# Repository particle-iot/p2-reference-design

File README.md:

# P2 evaluation board reference design

This board is a reference design for creating your own P2 base board. 

It is not available for purchase as a completed product; if you are interested in prototyping with the P2 we recommend using the Photon 2, which contains a P2 module on it, and has the same pinouts as the Feather connectors on this board.

This is a simple breakout board for Particle's P2 Wi-Fi module. It breaks out all of its pins via easy to use headers. The board features a USB port, a barrel jack power connector, buttons, and RGB LED as well as Feather, Grove, and Qwiic connectors for prototyping with external sensors, displays, etc..

- [P2 Datasheet](https://docs.particle.io/reference/datasheets/wi-fi/p2-datasheet/)
- [Particle hardware library for Eagle CAD](https://github.com/particle-iot/hardware-libraries)

## Schematic

The schematic files (*.sch) in Eagle CAD format are included in the **eagle** directory in this repository.

## Board layout

The board layout files (*.brd) in Eagle CAD format are included in the **eagle** directory in this repository. 

This is a 4-layer board, so you won't be able to edit the board using the free version of Autodesk Eagle, however gerber files are included in the **gerbers** directory if you want to fabricate this exact board.

The recommended stack-up is:

- DIELECTRIC = 3.61 at 1GHz
- TOP LAYER = 1.7MIL (1 OZ)
- PREPEG = 7.96MIL
- LAYER 2 = 0.68MIL (0.5 OZ)
- CORE = 47MIL
- LAYER 3 = 0.68MIL (0.5 OZ)
- PREPEG = 7.96MIL
- BOTTOM LAYER = 1.7MIL (1 OZ)

## Description

| Label | Description |
| :---: | :--- |
|     1 | USB |
|     2 | 5V Power In (optional) |
|     3 | P2 Module |
|     4 | External Wi-Fi and BLE antenna (optional) |
|     5 | Feather expansion connector |
|     6 | Qwiic I2C connector |
|     7 | Feather expansion connector |
|     8 | Grove expansion connector |
|     9 | Expansion header|
|    10 | RESET button |
|    11 | RGB LED |
|    12 | MODE button|
|    13 | SWD debugging connector |

If powering by USB, 500 mA is required. This a compatible with most USB hubs, computers, laptops, and chargers, but will not work with some low-power USB ports on some keyboards.
 
The P2 includes a built-in trace antenna that is used for both BLE and Wi-Fi. A U.FL connector is provided for an external antenna, if desired. The antenna selection must be made in software; the P2 will not automatically switch between built-in and external antennas. If using an external antenna, a dual-band (2.4 GHz and 5 GHz) antenna is required. The external antenna doesn't have to explicitly include BLE support, as the BLE frequencies are the same as 2.4 GHz Wi-Fi so all dual-band Wi-Fi antennas are compatible.

## Building user firmware

As of the time of writing (June 2022), P2 firmware can only be compiled using the cloud compiler.

### Using Particle Workbench

When using Particle Workbench, use the **Particle: Launch CLI** option from the Command Palette (Command-Shift-P or Ctrl-Shift-P). Then use the Particle CLI to generate a binary, as described in the next section.

### Using the Particle CLI

From the Particle CLI, you can use a command such as:

```
particle compile p2 . --target 5.3.1 --saveTo firmware.bin
```

Note that you must specify a target system version when building for the P2. If an upgrade of Device OS is required, it will be updated OTA.

### Using the Web IDE

From the Web IDE, select the Devices icon, then your P2 device, then target an appropriate firmware version, such as 5.3.1. If an upgrade of Device OS is required, it will be updated OTA.

## Expansion connectors

### Expansion header

If you are prototyping your own custom design you may want to use the 40-pin expansion header. It's a standard 20x2 female header, 0.1" pitch, that can accept male header pins or prototyping wires.

See the [P2 Datasheet](https://docs.particle.io/reference/datasheets/wi-fi/p2-datasheet/) for details about the pins. The gold boxes indicate the P2 pin numbers.

### Feather expansion

There are two socket for [Feather accessory boards](https://docs.particle.io/hardware/expansion/feather/). These are only for use with displays, sensors, storage, etc.. 

You must not plug a Particle device such as an Argon or Boron in this socket, as the device may be permanently damaged.

This will work with most Feather boards, however:

- The P2 does not support ADC inputs A3, A4, and A5.
- The P2 does not work with Feather accessories that use SPI1 on the Argon or Boron D pins.
- Some pins have different names which may require minor source code modifications. This includes and code that used Argon or Boron pins A3, A4, A5, or D8.

The pinouts of the Feather accessory socket correspond to pinouts of the Photon 2. See the [Photon 2 Datasheet](https://docs.particle.io/reference/datasheets/wi-fi/photon-2-datasheet/) and the [Argon to Photon 2 migration guide](https://docs.particle.io/hardware/migration-guides/photon-2-argon-migration-guide/) for more information.

Some pins in the same positions are named differently between the Argon/Boron and the Feather accessory socket/Photon 2:

| Argon Name | P2 Feather Socket Name |
| :---: | :---: |
| A3 | A5 |
| A4 | S4 |
| A5 | S3 |
| D8 | D10 |

Additionally, `D` pin aliases `D8` and higher are different, however these names are rarely used.

### Qwiic connector

[Qwiic](https://docs.particle.io/hardware/expansion/qwiic/) is a 3.3V I2C standard developed by SparkFun and adopted by other manufacturers. It's also compatible with Adafruit Stemma Qt expansion devices. You can use this to add displays, sensors, etc. and multiple devices can be connected to a single Qwiic port, as accessory boards have two connectors for chaining multiple sensors.

### Grove connector

The Grove connector allows [Grove accessories](https://docs.particle.io/reference/datasheets/accessories/gen3-accessories/#grove-starter-kit) to be added. Pins D0 and D1 are present on the connector. This allows the use of Grove I2C sensors.

If you are not using I2C elsewhere (Feather, Qwiic), you can use these pins as digital GPIO, or as analog inputs.

| Pin | I2C | Digital | Analog |
| :---: | :---: | :---: | :---: |
| GND | | | |
| 3V3 | | | |
| D0/SDA | SDA | D0 | A3 |
| D1/SCL | SCL | D1 | A4 |

## SWD debugging connector

The P2 eval board has a 10 pin debug connector that exposes the SWD interface of the MCU. This can be used to program the bootloader, device OS, or the user firmware using any standard SWD tools including the Particle Debugger, Segger J/LINK, or other CMSIS-DAP debuggers. It can also be used for source-level debugging using Particle Workbench.

Note that SWD is shared with GPIO pins D6 and D7, and by default SWD is only enabled while the bootloader is running, immediately at boot, and when in DFU mode (blinking yellow). Only Debug builds in Workbench have SWD enabled in when user firmware is running.

The SWO pin is not used on the P2.

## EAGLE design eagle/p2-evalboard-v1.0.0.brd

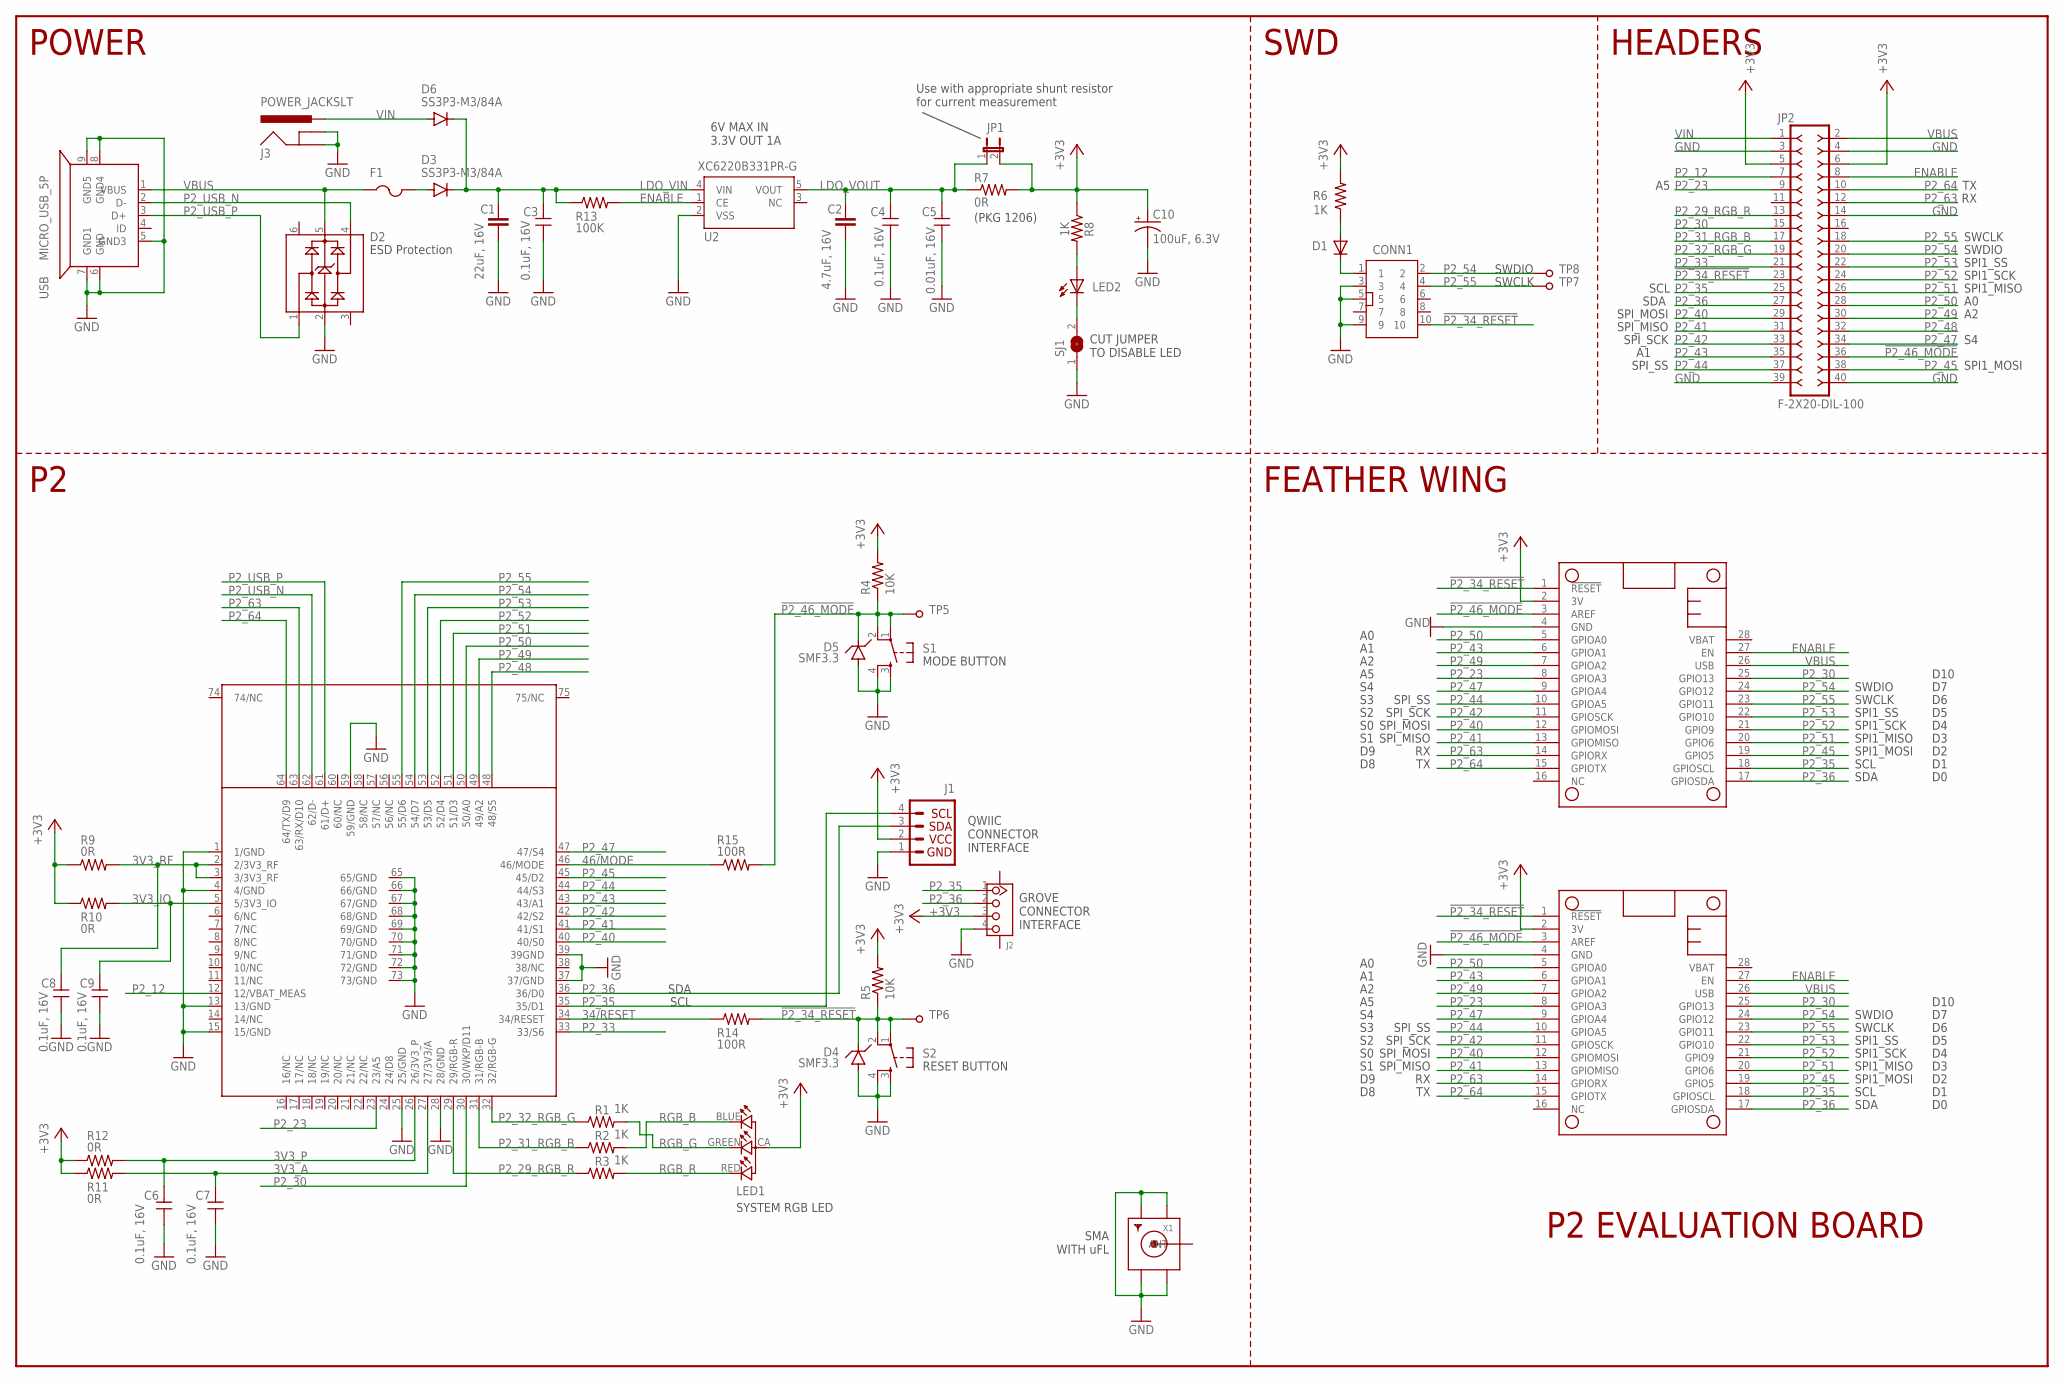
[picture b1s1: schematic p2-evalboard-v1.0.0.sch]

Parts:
C1: 22uF, 16V; C0805
C2: 4.7uF, 16V; C0805
C3, C4, C6, C7, C8, C9: 0.1uF, 16V; C0603_P
C5: 0.01uF, 16V; C0603_P
C10: 100uF, 6.3V; PANASONIC_C
CONN1: CONN5X2; CONN5X2_1.27
D1: DIODESOD-323F; SOD-323F
D2: MAX3207EAUT+T; SOT23-6
D3, D6: SS3P3-M3/84A; DIODE-DO-220AA(SMP)
D4, D5: SMF3.3; SOD-123FL
F1: PTCFUSE-1206; R1206
J1: QWIIC_CONNECTORJS-1MM; 1X04_1MM_RA
J2: 4P-SMD-2.0-90D; HW4-SMD-2.0-90D
J3: POWER_JACKSLT; POWER_JACK_SLOT
JP1: JUMPER2
JP2: F-2X20-DIL-100; DIL-100-2X20
LED1: RGB-LED-CLMVB-FKARGB; PLCC4-2MM-RGB
LED2: LEDCHIPLED_0603; CHIPLED_0603
MS1, MS2: FEATHERWING_NODIM; FEATHERWING_DIM
R1, R2, R3, R6, R8: 1K; R0603_P
R4, R5: 10K; R0603_P
R7: 0R; R1206
R9, R10, R11, R12: 0R; R0603_P
R13: 100K; R0603_P
R14, R15: 100R; R0603_P
S1, S2: TAC_SWITCHSMD; TACTILE_SWITCH_SMD
SJ1: SOLDERJUMPERCLOSED; SOLDERJUMPER_CLOSEDWIRE
TP5, TP6, TP7, TP8: TP-1.5MM; TP
U1: P2; TRON
U2: XC6220B331PR-G; SOT-89-5_TOR-M
USB: MICRO_USB_5P; MICRO_USB
X1: SMACONNECTOR; SMA90_DIP

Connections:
3V3_A: C7.2, R11.2, U1.27 (27/3V3/A)
3V3_IO: C9.2, R10.2, U1.5 (5/3V3_IO)
3V3_P: C6.2, R12.2, U1.26 (26/3V3_P)
3V3_RF: C8.2, R9.2, U1.2 (2/3V3_RF), U1.3 (3/3V3_RF)
34/RESET: R14.1, U1.34 (34/RESET)
46/MODE: R15.1, U1.46 (46/MODE)
!P2_34_RESET: CONN1.10, D4.C, JP2.23, MS1.1 (!RESET), MS2.1 (!RESET), R5.1, R14.2, S2.1, S2.2, TP6.TP
!P2_46_MODE: D5.C, JP2.36, MS1.3 (AREF), MS2.3 (AREF), R4.1, R15.2, S1.1, S1.2, TP5.TP
+3V3: C10.+, J1.2 (VCC), J2.3, JP1.2, JP2.5, JP2.6, LED1.CA (1), MS1.2 (3V), MS2.2 (3V), R4.2, R5.2, R6.2, R7.2, R8.1, R9.1, R10.1, R11.1, R12.1
ENABLE: JP2.8, MS1.27 (EN), MS2.27 (EN), R13.2, U2.1 (CE)
GND: C1.2, C2.2, C3.1, C4.1, C5.1, C6.1, C7.1, C8.1, C9.1, C10.-, CONN1.3, CONN1.5, CONN1.9, D2.2, D4.A, D5.A, J1.1 (GND), J2.4, J3.GND@1 (GNDBREAK), J3.GND@2 (GND), JP2.3, JP2.4, JP2.14, JP2.39, JP2.40, MS1.4 (GND), MS2.4 (GND), S1.3, S1.4, S2.3, S2.4, SJ1.1, U1.1 (1/GND), U1.4 (4/GND), U1.13 (13/GND), U1.15 (15/GND), U1.25 (25/GND), U1.28 (28/GND), U1.37 (37/GND), U1.39 (39GND), U1.59 (59/GND), U1.65 (65/GND), U1.66 (66/GND), U1.67 (67/GND), U1.68 (68/GND), U1.69 (69/GND), U1.70 (70/GND), U1.71 (71/GND), U1.72 (72/GND), U1.73 (73/GND), U2.2 (VSS), USB.5 (GND3), USB.6 (GND), USB.7 (GND1), USB.8 (GND4), USB.9 (GND5), X1.GND1, X1.GND2, X1.GND3, X1.GND4
LDO_VIN: C1.1, C3.2, D3.CATHODE, D6.CATHODE, R13.1, U2.4 (VIN)
LDO_VOUT: C2.1, C4.2, C5.2, JP1.1, R7.1, U2.5 (VOUT)
unnamed: CONN1.1, D1.C
unnamed: D1.A, R6.1
unnamed: LED2.C, SJ1.2
unnamed: D3.ANODE, F1.2
unnamed: LED2.A, R8.2
P2_12: JP2.7, U1.12 (12/VBAT_MEAS)
P2_23: JP2.9, MS1.8 (GPIOA3), MS2.8 (GPIOA3), U1.23 (23/A5)
P2_29_RGB_R: JP2.13, R3.1, U1.29 (29/RGB-R)
P2_30: JP2.15, MS1.25 (GPIO13), MS2.25 (GPIO13), U1.30 (30/WKP/D11)
P2_31_RGB_B: JP2.17, R2.1, U1.31 (31/RGB-B)
P2_32_RGB_G: JP2.19, R1.1, U1.32 (32/RGB-G)
P2_33: JP2.21, U1.33 (33/S6)
P2_35: J1.4 (SCL), J2.1, JP2.25, MS1.18 (GPIOSCL), MS2.18 (GPIOSCL), U1.35 (35/D1)
P2_36: J1.3 (SDA), J2.2, JP2.27, MS1.17 (GPIOSDA), MS2.17 (GPIOSDA), U1.36 (36/D0)
P2_40: JP2.29, MS1.12 (GPIOMOSI), MS2.12 (GPIOMOSI), U1.40 (40/S0)
P2_41: JP2.31, MS1.13 (GPIOMISO), MS2.13 (GPIOMISO), U1.41 (41/S1)
P2_42: JP2.33, MS1.11 (GPIOSCK), MS2.11 (GPIOSCK), U1.42 (42/S2)
P2_43: JP2.35, MS1.6 (GPIOA1), MS2.6 (GPIOA1), U1.43 (43/A1)
P2_44: JP2.37, MS1.10 (GPIOA5), MS2.10 (GPIOA5), U1.44 (44/S3)
P2_45: JP2.38, MS1.19 (GPIO5), MS2.19 (GPIO5), U1.45 (45/D2)
P2_47: JP2.34, MS1.9 (GPIOA4), MS2.9 (GPIOA4), U1.47 (47/S4)
P2_48: JP2.32, U1.48 (48/S5)
P2_49: JP2.30, MS1.7 (GPIOA2), MS2.7 (GPIOA2), U1.49 (49/A2)
P2_50: JP2.28, MS1.5 (GPIOA0), MS2.5 (GPIOA0), U1.50 (50/A0)
P2_51: JP2.26, MS1.20 (GPIO6), MS2.20 (GPIO6), U1.51 (51/D3)
P2_52: JP2.24, MS1.21 (GPIO9), MS2.21 (GPIO9), U1.52 (52/D4)
P2_53: JP2.22, MS1.22 (GPIO10), MS2.22 (GPIO10), U1.53 (53/D5)
P2_54: CONN1.2, JP2.20, MS1.24 (GPIO12), MS2.24 (GPIO12), TP8.TP, U1.54 (54/D7)
P2_55: CONN1.4, JP2.18, MS1.23 (GPIO11), MS2.23 (GPIO11), TP7.TP, U1.55 (55/D6)
P2_63: JP2.12, MS1.14 (GPIORX), MS2.14 (GPIORX), U1.63 (63/RX/D10)
P2_64: JP2.10, MS1.15 (GPIOTX), MS2.15 (GPIOTX), U1.64 (64/TX/D9)
P2_USB_N: D2.4, U1.62 (62/D-), USB.2 (D-)
P2_USB_P: D2.1, U1.61 (61/D+), USB.3 (D+)
RGB_B: LED1.BLUE (2), R2.2
RGB_G: LED1.GREEN (3), R1.2
RGB_R: LED1.RED (4), R3.2
VBUS: D2.5, F1.1, JP2.2, MS1.26 (USB), MS2.26 (USB), USB.1 (VBUS)
VIN: D6.ANODE, J3.PWR, JP2.1

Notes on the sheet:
(PKG 1206)
CUT JUMPER TO DISABLE LED
Use with appropriate shunt resistor for current measurement
ESD Protection
QWIIC CONNECTOR INTERFACE
SMA WITH uFL
SDA
SCL
P2 EVALUATION BOARD
6V MAX IN 3.3V OUT 1A
SYSTEM RGB LED
MODE BUTTON
RESET BUTTON
SWDIO
SWCLK
SPI_MISO
SPI_MOSI
SPI_SCK
SPI_SS
POWER
SWD
FEATHER WING
GROVE CONNECTOR INTERFACE
SPI1_SCK
SPI1_MOSI
SPI1_MISO
SPI1_SS
D10
HEADERS

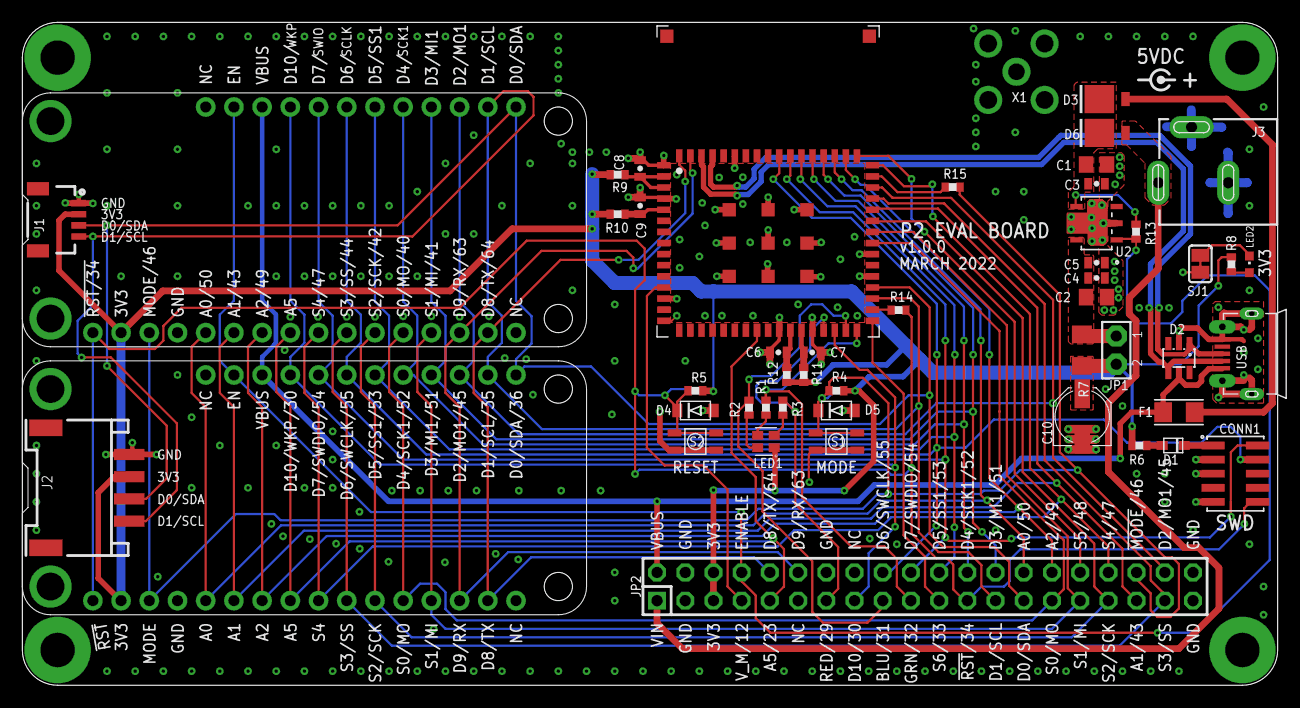
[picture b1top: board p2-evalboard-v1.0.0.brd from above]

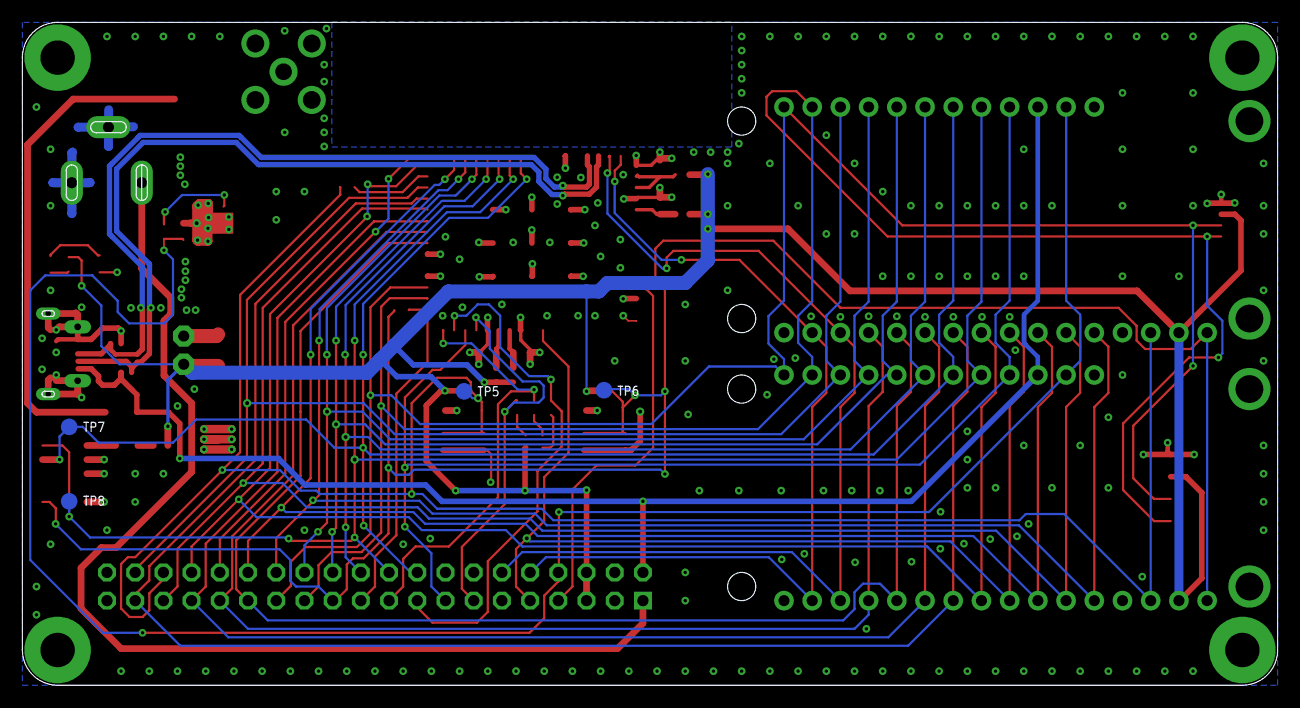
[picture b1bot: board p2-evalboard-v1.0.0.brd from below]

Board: 4 copper layers, 113.0 x 59.7 mm, 53 parts (4 on the bottom side), 51 nets.

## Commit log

2023-05-08 Initial version

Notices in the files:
parts and their libraries:
SparkFun-Connectors: Licensing: Creative Commons ShareAlike 4.0 International - https://creativecommons.org/licenses/by-sa/4.0
microbuilder: This work is placed in the public domain, and may be freely used for commercial and non-commercial work with the following conditions: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
